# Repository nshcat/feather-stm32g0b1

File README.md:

# prop-devboard

A STM32G0B1-based development board meant for prop making, inspired by Adafruits Feather series of boards

## Features 
* Compatible with most (if not all!) Feather Wing addon boards
* Two independant QWIIC ports, connected to `I2C1` and `I2C2`, respectively
* +3V3 power supply that can deliver 500mA of power
* JST PH2.0 port for LiPo battery, and circuitry for powering off battery:
     * Automatic and safe switching between USB and LiPo battery as power source, even with both connected at the same time
     * Safe battery charging using `MCP73831` over the USB-C port
     * Battery level monitoring using `MAX17048G`
* STDC14 programming header, compatible with STLINK-V3MINIE
* Both HSE (8 MHz) and LSE (32.768 KHz) crystals
* ST M24512-DF 512Kbit I2C EEPROM

## Images

")

")

")

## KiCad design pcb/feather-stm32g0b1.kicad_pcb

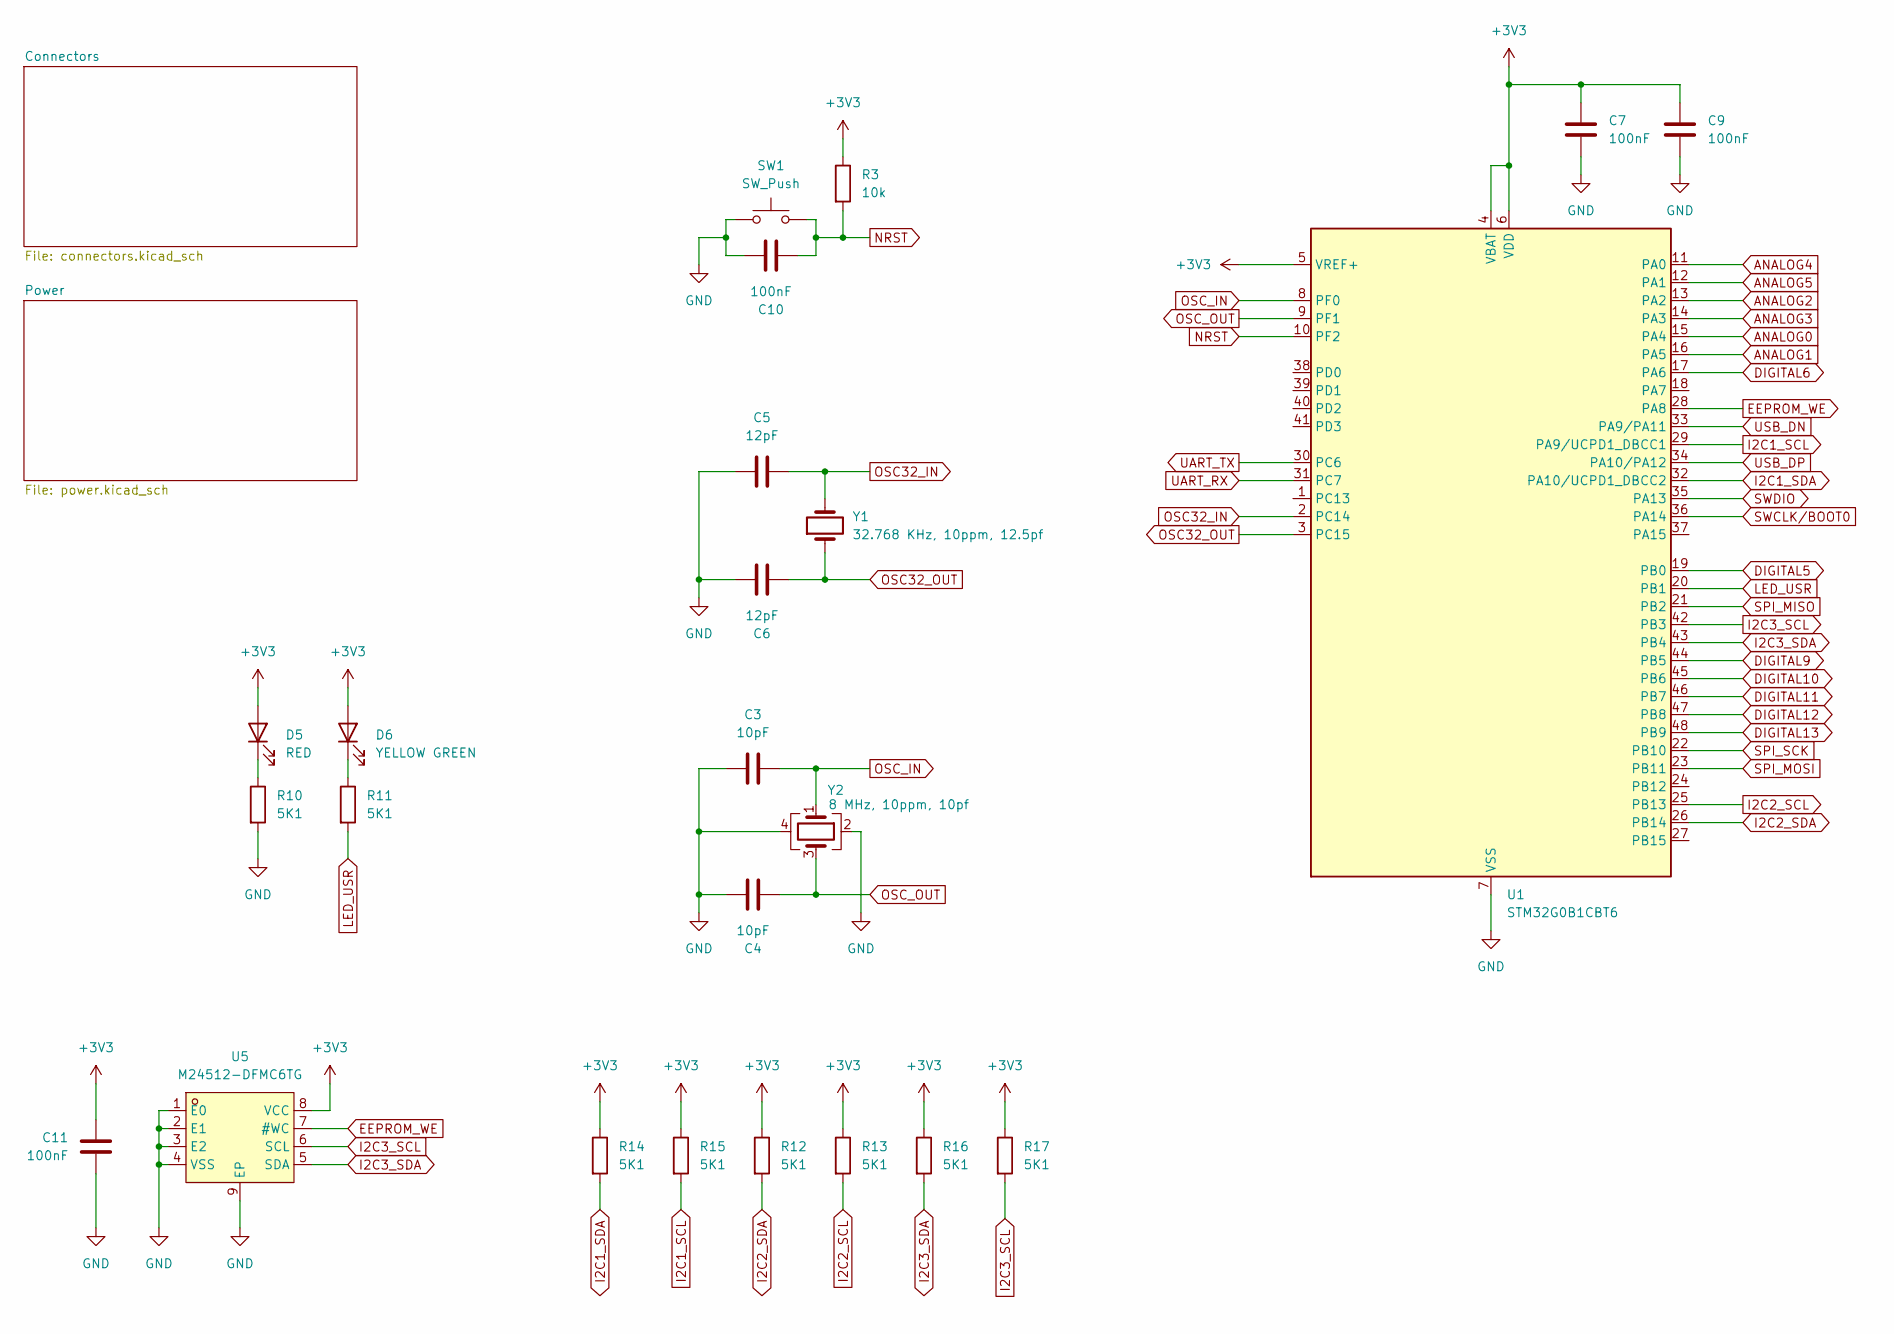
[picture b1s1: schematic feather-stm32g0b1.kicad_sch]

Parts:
C3, C4: 10pF; C_0402_1005Metric; LCSC Part # C32949
C5, C6: 12pF; C_0402_1005Metric; LCSC Part # C1547
C7, C9, C10, C11: 100nF; C_0402_1005Metric; LCSC Part # C1525
D5: RED; LED_0402_1005Metric; LCSC Part # C130719
D6: YELLOW GREEN; LED_0402_1005Metric; LCSC Part # C130722
R3: 10k; R_0402_1005Metric; LCSC Part # C25744
R10, R11, R12, R13, R14, R15, R16, R17: 5K1; R_0402_1005Metric; LCSC Part # C25905
SW1: SW_Push; WUERTH_434153017835; LCSC Part # C2680612
U1: STM32G0B1CBT6; LQFP-48_7x7mm_P0.5mm; LCSC Part # C2847904
U5: M24512-DFMC6TG; DFN-8_L3.0-W2.0-P0.50-BL-EP; MPN M24512-DFMC6TG; LCSC Part C222237
Y1: 32.768 KHz, 10ppm, 12.5pf; Crystal_SMD_3215-2Pin_3.2x1.5mm; LCSC Part # C32346
Y2: 8 MHz, 10ppm, 10pf; Crystal_SMD_3225-4Pin_3.2x2.5mm; LCSC Part # C400090

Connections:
+3V3: C7.2, C9.2, C11.2, D5.2 (A), D6.2 (A), R3.1, R12.1, R13.1, R14.1, R15.1, R16.1, R17.1, U1.4 (VBAT), U1.5 (VREF+), U1.6 (VDD), U5.8 (VCC); also elsewhere on the board
ANALOG0: U1.15 (PA4); also elsewhere on the board
ANALOG1: U1.16 (PA5); also elsewhere on the board
ANALOG2: U1.13 (PA2); also elsewhere on the board
ANALOG3: U1.14 (PA3); also elsewhere on the board
ANALOG4: U1.11 (PA0); also elsewhere on the board
ANALOG5: U1.12 (PA1); also elsewhere on the board
DIGITAL5: U1.19 (PB0); also elsewhere on the board
DIGITAL6: U1.17 (PA6); also elsewhere on the board
DIGITAL9: U1.44 (PB5); also elsewhere on the board
DIGITAL10: U1.45 (PB6); also elsewhere on the board
DIGITAL11: U1.46 (PB7); also elsewhere on the board
DIGITAL12: U1.47 (PB8); also elsewhere on the board
DIGITAL13: U1.48 (PB9); also elsewhere on the board
EEPROM_WE: U1.28 (PA8), U5.7 (#WC)
GND: C3.2, C4.2, C5.1, C6.2, C7.1, C9.1, C10.1, C11.1, R10.2, SW1.2, U1.7 (VSS), U5.1 (E0), U5.2 (E1), U5.3 (E2), U5.4 (VSS), U5.9 (EP), Y2.2, Y2.4; also elsewhere on the board
I2C1_SCL: R15.2, U1.29 (PA9/UCPD1_DBCC1); also elsewhere on the board
I2C1_SDA: R14.2, U1.32 (PA10/UCPD1_DBCC2); also elsewhere on the board
I2C2_SCL: R13.2, U1.25 (PB13); also elsewhere on the board
I2C2_SDA: R12.2, U1.26 (PB14); also elsewhere on the board
I2C3_SCL: R17.2, U1.42 (PB3), U5.6 (SCL); also elsewhere on the board
I2C3_SDA: R16.2, U1.43 (PB4), U5.5 (SDA); also elsewhere on the board
LED_USR: R11.2, U1.20 (PB1)
NRST: C10.2, R3.2, SW1.1, U1.10 (PF2); also elsewhere on the board
unnamed: D5.1 (K), R10.1
unnamed: D6.1 (K), R11.1
OSC32_IN: C5.2, U1.2 (PC14), Y1.2
OSC32_OUT: C6.1, U1.3 (PC15), Y1.1
OSC_IN: C3.1, U1.8 (PF0), Y2.1
OSC_OUT: C4.1, U1.9 (PF1), Y2.3
SPI_MISO: U1.21 (PB2); also elsewhere on the board
SPI_MOSI: U1.23 (PB11); also elsewhere on the board
SPI_SCK: U1.22 (PB10); also elsewhere on the board
SWCLK/BOOT0: U1.36 (PA14); also elsewhere on the board
SWDIO: U1.35 (PA13); also elsewhere on the board
UART_RX: U1.31 (PC7); also elsewhere on the board
UART_TX: U1.30 (PC6); also elsewhere on the board
USB_DN: U1.33 (PA9/PA11); also elsewhere on the board
USB_DP: U1.34 (PA10/PA12); also elsewhere on the board

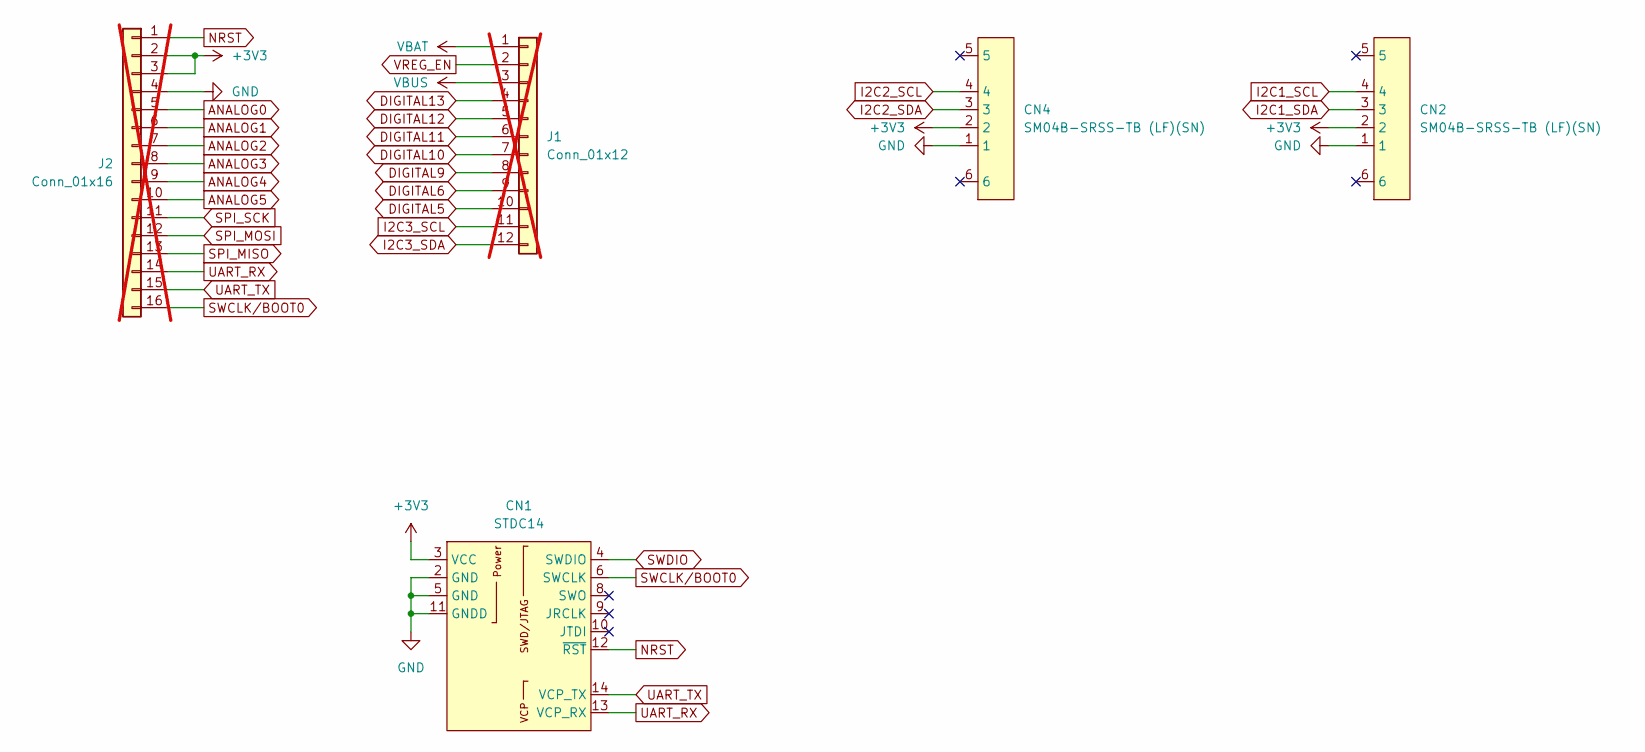
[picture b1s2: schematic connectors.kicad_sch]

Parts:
CN1: STDC14; HDR-SMD_14P-P1.27-V-M-R2-C7-LS5.8_FTS-107-03-X-DV; LCSC Part # C46971079
CN2, CN4: SM04B-SRSS-TB (LF)(SN); CONN-SMD_4P-P1.00_SM04B-SRSS-TB-LF-SN; LCSC Part C19270571
J1: Conn_01x12; PinHeader_1x12_P2.54mm_Vertical; not fitted
J2: Conn_01x16; PinHeader_1x16_P2.54mm_Vertical; not fitted

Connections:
+3V3: CN1.3 (VCC), CN2.2, CN4.2, J2.2, J2.3; also elsewhere on the board
ANALOG0: J2.5; also elsewhere on the board
ANALOG1: J2.6; also elsewhere on the board
ANALOG2: J2.7; also elsewhere on the board
ANALOG3: J2.8; also elsewhere on the board
ANALOG4: J2.9; also elsewhere on the board
ANALOG5: J2.10; also elsewhere on the board
DIGITAL5: J1.10; also elsewhere on the board
DIGITAL6: J1.9; also elsewhere on the board
DIGITAL9: J1.8; also elsewhere on the board
DIGITAL10: J1.7; also elsewhere on the board
DIGITAL11: J1.6; also elsewhere on the board
DIGITAL12: J1.5; also elsewhere on the board
DIGITAL13: J1.4; also elsewhere on the board
GND: CN1.2 (GND), CN1.5 (GND), CN1.11 (GNDD), CN2.1, CN4.1, J2.4; also elsewhere on the board
I2C1_SCL: CN2.4; also elsewhere on the board
I2C1_SDA: CN2.3; also elsewhere on the board
I2C2_SCL: CN4.4; also elsewhere on the board
I2C2_SDA: CN4.3; also elsewhere on the board
I2C3_SCL: J1.11; also elsewhere on the board
I2C3_SDA: J1.12; also elsewhere on the board
NRST: CN1.12 (~RST), J2.1; also elsewhere on the board
SPI_MISO: J2.13; also elsewhere on the board
SPI_MOSI: J2.12; also elsewhere on the board
SPI_SCK: J2.11; also elsewhere on the board
SWCLK/BOOT0: CN1.6 (SWCLK), J2.16; also elsewhere on the board
SWDIO: CN1.4 (SWDIO); also elsewhere on the board
UART_RX: CN1.13 (VCP_RX), J2.14; also elsewhere on the board
UART_TX: CN1.14 (VCP_TX), J2.15; also elsewhere on the board
VBAT: J1.1; also elsewhere on the board
VBUS: J1.3; also elsewhere on the board
VREG_EN: J1.2; also elsewhere on the board

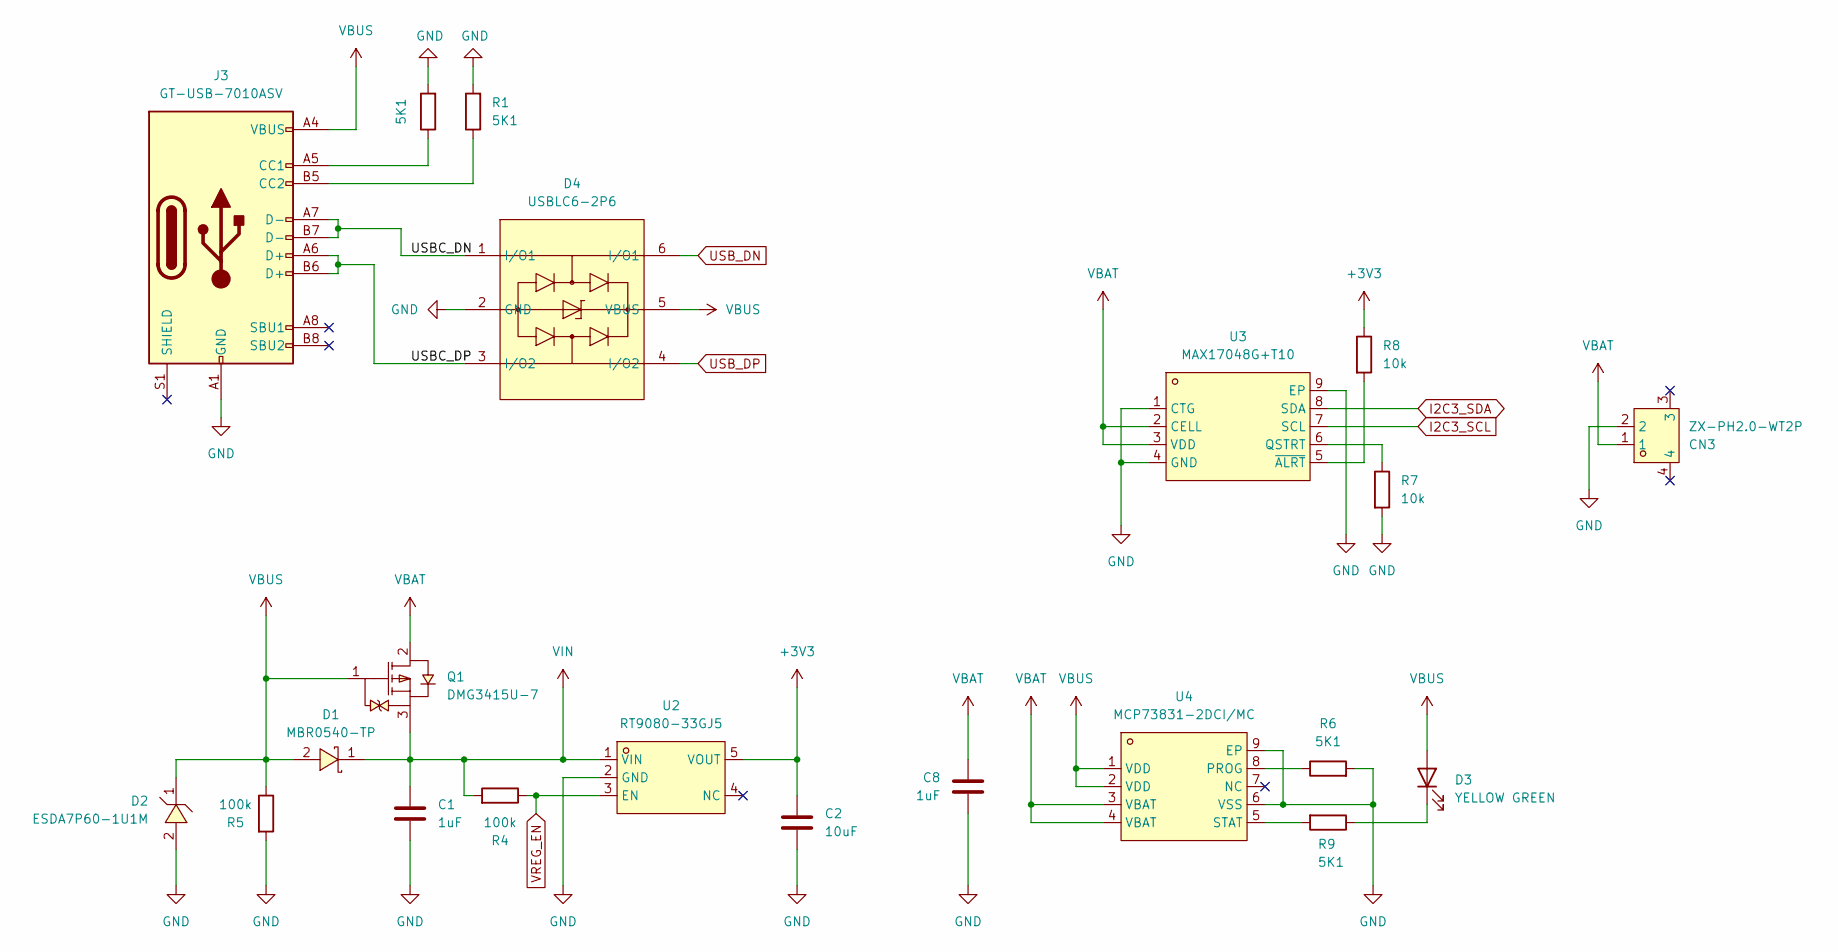
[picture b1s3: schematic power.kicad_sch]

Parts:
C1, C8: 1uF; C_0402_1005Metric; LCSC Part # C14445
C2: 10uF; C_0402_1005Metric; LCSC Part # C15525
CN3: ZX-PH2.0-WT2P; CONN-SMD_PH-2AWT; LCSC Part C19633668
D1: MBR0540-TP; SOD-123_L2.7-W1.6-LS3.7-RD; LCSC Part C78744
D2: ESDA7P60-1U1M; D1610-RD; LCSC Part C1975146
D3: YELLOW GREEN; LED_0402_1005Metric; LCSC Part # C130722
D4: USBLC6-2P6; SOT-666-6_L1.6-W1.2-P0.50-LS1.6-BR; LCSC Part C15999
J3: GT-USB-7010ASV; USB_C_Receptacle_G-Switch_GT-USB-7010ASV; LCSC Part # C2988369
Q1: DMG3415U-7; SOT-23-3_L2.9-W1.6-P1.90-LS2.8-BR-CW; LCSC Part C96616
R1, R2, R6, R9: 5K1; R_0402_1005Metric; LCSC Part # C25905
R4: 100k; R_0402_1005Metric; LCSC Part # C60491
R5: 100k; R_0402_1005Metric; LCSC Part # C25741
R7, R8: 10k; R_0402_1005Metric; LCSC Part # C25744
U2: RT9080-33GJ5; TSOT-23-5_L2.9-W1.6-P0.95-LS2.8-BL; LCSC Part C841192
U3: MAX17048G+T10; TDFN-8_L2.0-W2.0-P0.50-BL-EP1.2; LCSC Part C2682616
U4: MCP73831-2DCI/MC; DFN-8_L3.0-W2.0-P0.50-BL-EP1.6; LCSC Part C635037

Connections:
+3V3: C2.2, R8.1, U2.5 (VOUT); also elsewhere on the board
/Power/USBC_DN: D4.1 (I/O1), J3.A7 (D-), J3.B7 (D-)
/Power/USBC_DP: D4.3 (I/O2), J3.A6 (D+), J3.B6 (D+)
GND: C1.1, C2.1, C8.1, CN3.2, D2.2, D4.2 (GND), J3.A1 (GND), J3.A12 (GND), J3.B1 (GND), J3.B12 (GND), R1.2, R2.2, R5.2, R6.2, R7.2, U2.2 (GND), U3.1 (CTG), U3.4 (GND), U3.9 (EP), U4.6 (VSS), U4.9 (EP); also elsewhere on the board
I2C3_SCL: U3.7 (SCL); also elsewhere on the board
I2C3_SDA: U3.8 (SDA); also elsewhere on the board
unnamed: D3.1 (K), R9.1
unnamed: J3.A5 (CC1), R2.1
unnamed: J3.B5 (CC2), R1.1
unnamed: R7.1, U3.6 (QSTRT)
unnamed: R8.2, U3.5 (~ALRT)
unnamed: R6.1, U4.8 (PROG)
unnamed: R9.2, U4.5 (STAT)
USB_DN: D4.6 (I/O1); also elsewhere on the board
USB_DP: D4.4 (I/O2); also elsewhere on the board
VBAT: C8.2, CN3.1, Q1.2, U3.2 (CELL), U3.3 (VDD), U4.3 (VBAT), U4.4 (VBAT); also elsewhere on the board
VBUS: D1.2, D2.1, D3.2 (A), D4.5 (VBUS), J3.A4 (VBUS), J3.A9 (VBUS), J3.B4 (VBUS), J3.B9 (VBUS), Q1.1, R5.1, U4.1 (VDD), U4.2 (VDD); also elsewhere on the board
VIN: C1.2, D1.1, Q1.3, R4.2, U2.1 (VIN)
VREG_EN: R4.1, U2.3 (EN); also elsewhere on the board

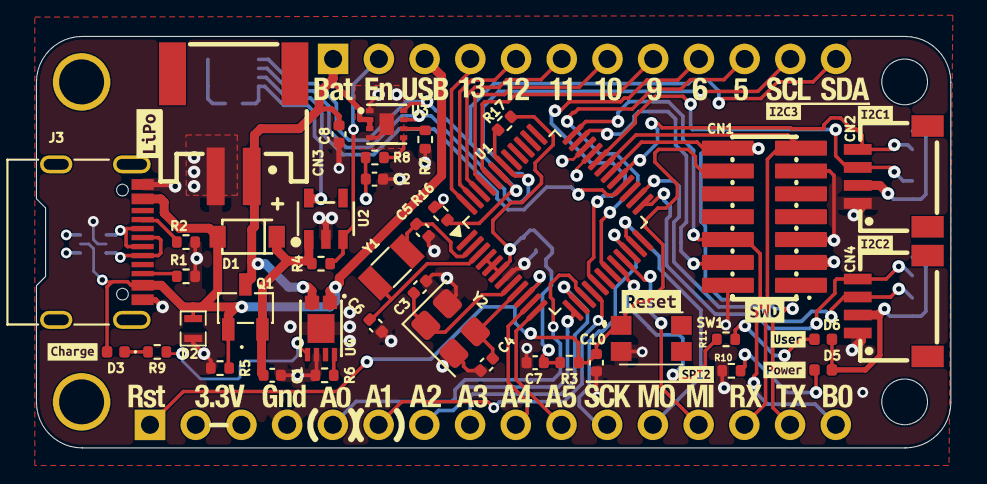
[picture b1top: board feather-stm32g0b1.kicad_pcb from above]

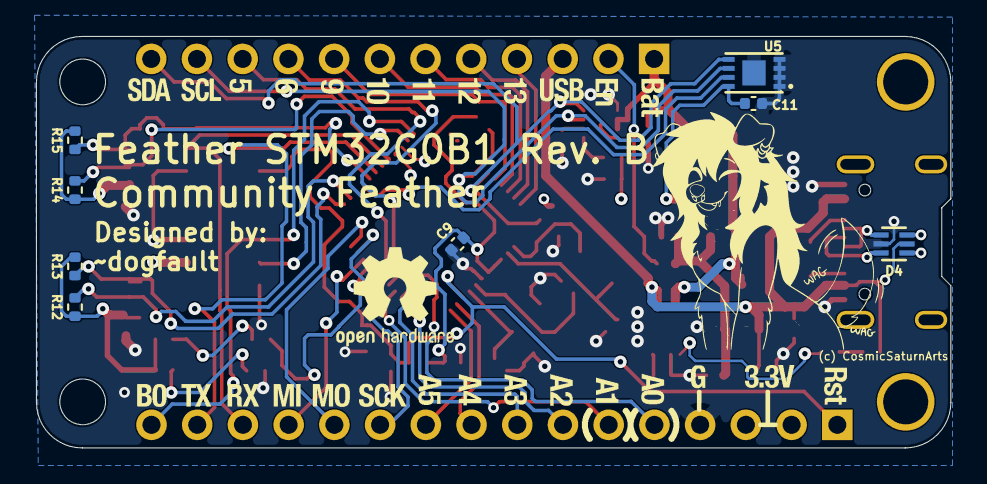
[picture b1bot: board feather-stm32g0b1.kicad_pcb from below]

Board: 4 copper layers, 50.8 x 22.9 mm, 62 parts (9 on the bottom side), 52 nets.

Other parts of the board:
U$24: PINLABELS_TOP
U$40: Val**; PINLABELS_BOT
kibuzzard-69DFDE44: G***; kibuzzard-69DFDE44
kibuzzard-69DFDEC0: G***; kibuzzard-69DFDEC0
kibuzzard-69DFDEEF: G***; kibuzzard-69DFDEEF
kibuzzard-69DFDF04: G***; kibuzzard-69DFDF04
kibuzzard-69DFDF67: G***; kibuzzard-69DFDF67
kibuzzard-69DFDFA3: G***; kibuzzard-69DFDFA3
kibuzzard-69DFDFE1: G***; kibuzzard-69DFDFE1
kibuzzard-69DFDFEF: G***; kibuzzard-69DFDFEF
kibuzzard-69DFE1A1: G***; kibuzzard-69DFE1A1
kibuzzard-69DFE014: G***; kibuzzard-69DFE014

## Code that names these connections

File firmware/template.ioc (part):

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Mcu.Name=STM32G0B1C(B-C-E)Tx
Mcu.Package=LQFP48
Mcu.UserName=STM32G0B1CBTx
PA0.Mode=IN0
PA0.Signal=ADC1_IN0
PA1.Mode=IN1
PA1.Signal=ADC1_IN1
PA10.Mode=I2C
PA10.Signal=I2C1_SDA
PA11\ [PA9].Mode=Device
PA11\ [PA9].Signal=USB_DM
PA12\ [PA10].Mode=Device
PA12\ [PA10].Signal=USB_DP
PA13.Mode=Serial_Wire
PA13.Signal=SYS_SWDIO
PA14-BOOT0.Mode=Serial_Wire
PA14-BOOT0.Signal=SYS_SWCLK
PA2.Mode=IN2
PA2.Signal=ADC1_IN2
PA3.Mode=IN3
PA3.Signal=ADC1_IN3
PA4.Mode=IN4
PA4.Signal=ADC1_IN4
PA5.Mode=IN5
PA5.Signal=ADC1_IN5
PA9.Mode=I2C
PA9.Signal=I2C1_SCL
PB10.Mode=Full_Duplex_Master
PB10.Signal=SPI2_SCK
PB11.Mode=Full_Duplex_Master
PB11.Signal=SPI2_MOSI
PB13.Mode=I2C
PB13.Signal=I2C2_SCL
PB14.Mode=I2C
PB14.Signal=I2C2_SDA
PB2.Mode=Full_Duplex_Master
PB2.Signal=SPI2_MISO
PB3.Mode=I2C
PB3.Signal=I2C3_SCL
PB4.Mode=I2C
PB4.Signal=I2C3_SDA
PC14-OSC32_IN\ (PC14).Mode=LSE-External-Oscillator
PC14-OSC32_IN\ (PC14).Signal=RCC_OSC32_IN
PC15-OSC32_OUT\ (PC15).Mode=LSE-External-Oscillator
PC15-OSC32_OUT\ (PC15).Signal=RCC_OSC32_OUT
PC6.Mode=Asynchronous
PC6.Signal=LPUART2_TX
PC7.Mode=Asynchronous
PC7.Signal=LPUART2_RX
PF0-OSC_IN\ (PF0).Mode=HSE-External-Oscillator
PF0-OSC_IN\ (PF0).Signal=RCC_OSC_IN
PF1-OSC_OUT\ (PF1).Mode=HSE-External-Oscillator
PF1-OSC_OUT\ (PF1).Signal=RCC_OSC_OUT
RCC.HSE_VALUE=8000000
RCC.SYSCLKFreq_VALUE=16000000
board=custom

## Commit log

2026-02-20 Initial work on PCB
2026-02-20 Added production files folder to .gitignore
2026-02-23 Work on schematics
2026-02-25 Added CubeMX template, and more schematics work
2026-02-25 Lots of work on schematics
2026-02-27 Added TLV755 LDO symbol and footprint
2026-02-27 Mostly finished PCB layout
2026-02-27 Added documentation
2026-02-27 Added USB support
2026-02-27 Updated documentation
2026-02-27 Updated documentation again
2026-02-27 Improved track connection to USB VBUS pads (was too thin)
2026-02-28 Added power and status LEDs to the design
2026-02-28 Fixed screenshot
2026-02-28 Added revision number
2026-03-01 Fixed various issues encountered during DFM checks
2026-03-04 Added silkscreen art to pcb
2026-03-04 Updated documentation, II
2026-03-04 Fixed MCU power pins not being connected correctly
2026-03-07 Fixed wrong polarity of the battery connector, uffff
2026-03-14 Updated silkscreen to show battery polarity, as well as I2C and SPI peripheral numbers
2026-03-21 Renamed kicad project
2026-03-27 Lots more work on RevB schematics and pcb
2026-03-27 Small test commit
2026-03-31 Added black clone JST PH 2 pin male header
2026-04-02 Added black JST SH clone pin header
2026-04-02 Fixed clone JST PH header footprint orientation
2026-04-02 Smaller fixes to JST PH header footprint
2026-04-02 Switched battery and QWIIC connectors to black ones, and fixed their positioning to not obstruct bolt heads when M2.5 cylindrical bolts are used to mount the board
2026-04-02 Added I2C pull ups, extra bypass capacitance for the MCU and increased the LDO output capacitance
2026-04-02 More PCB layout updates
2026-04-02 Some minor pcb changes
2026-04-15 Upgraded kicad project to kicad 10
2026-04-15 Updated some diode symbols that were skewed
2026-04-15 Used kibuzzard to generate nice labels for buttons, ports and leds
2026-04-16 Added I2C EEPROM to the board
2026-04-16 Updated README and images
